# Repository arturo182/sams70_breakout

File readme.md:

# Atmel/Microchip SAM S70 breakout board

A fairly simple board which breaks out all the pins of the chip.

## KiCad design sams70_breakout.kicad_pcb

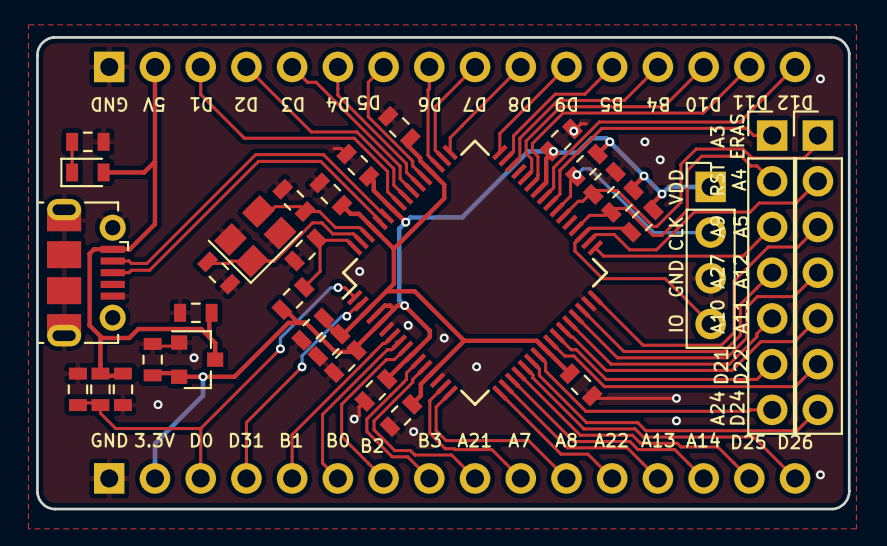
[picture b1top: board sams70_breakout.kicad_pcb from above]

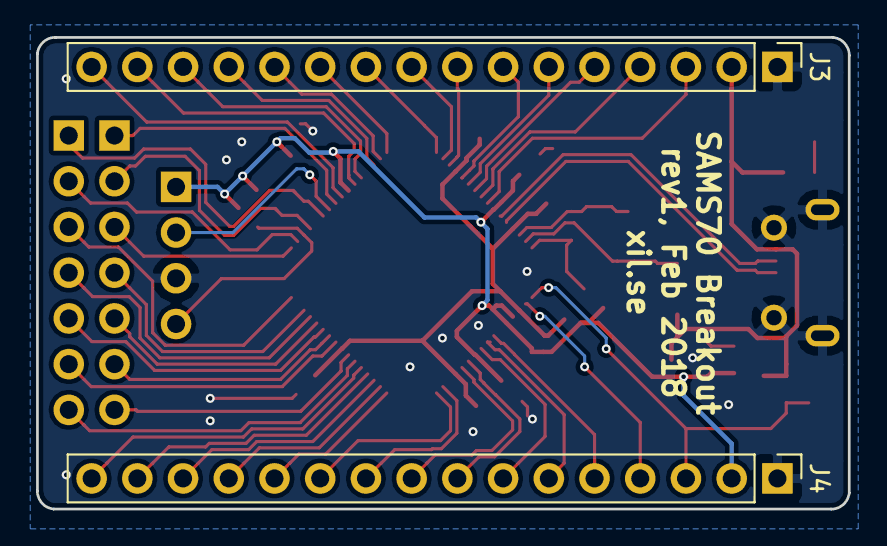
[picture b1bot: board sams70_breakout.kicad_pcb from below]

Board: 2 copper layers, 45.1 x 26.2 mm, 34 parts (2 on the bottom side), 54 nets.

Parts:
C1, C14: 4.7uF; C_0603_1608Metric
C2, C3: 12pF; C_0603_1608Metric
C4, C5, C6, C7, C8, C9, C11, C12, C13: 0.1uF; C_0603_1608Metric
C10, C15, C16: 1uF; C_0603_1608Metric
D1: PWR; LED_0603_1608Metric
J1: USB_OTG; USB_Micro-B_Molex-105017-0001
J2: Conn_01x04; PinHeader_1x04_P2.54mm_Vertical
J3, J4: Conn_01x16; PinHeader_1x16_P2.54mm_Vertical
J5, J6: Conn_01x07; PinHeader_1x07_P2.54mm_Vertical
R1: 15k; R_0603_1608Metric
R2: 22k; R_0603_1608Metric
R3, R5, R6, R7: 10K; R_0603_1608Metric
R4: 2.2R; R_0603_1608Metric
R8: 560R; R_0603_1608Metric
U1: ATSAME70J20A-AN; LQFP-64_10x10mm_P0.5mm
U2: XC6206P332MR; SOT-23
Y1: 16MHz; Crystal_SMD_3225-4Pin_3.2x2.5mm

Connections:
+1V2: C4.1, C5.1, C6.1, C10.2, C11.2, C13.2, U1.3, U1.13, U1.24, U1.52, U1.61
+3V3: C7.1, C8.1, C9.1, C12.2, C16.1, J2.1, J4.2, R3.1, R4.1, R6.1, R7.1, U1.4, U1.5, U1.10, U1.42, U1.58, U2.2
/ERASE: J6.1, R5.1, U1.38
/PA3: J5.1, U1.40
/PA4: J6.2, U1.34
/PA5: J6.3, U1.32
/PA7: J4.10, U1.15
/PA8: J4.11, U1.16
/PA9: J5.3, U1.33
/PA10: J5.5, U1.28
/PA11: J6.5, U1.27
/PA12: J6.4, U1.29
/PA13: J4.13, U1.18
/PA14: J4.14, U1.19
/PA21: J4.9, U1.12
/PA22: J4.12, U1.17
/PA24: J5.7, U1.23
/PA27: J5.4, U1.30
/PB0: J4.6, U1.8
/PB1: J4.5, U1.7
/PB2: J4.7, U1.9
/PB3: J4.8, U1.11
/PB4: J3.13, U1.46
/PB5: J3.12, U1.47
/PD0: J4.3, R1.1, R2.1, U1.1
/PD1: J3.3, U1.57
/PD2: J3.4, U1.56
/PD3: J3.5, U1.55
/PD4: J3.6, U1.54
/PD5: J3.7, U1.53
/PD6: J3.8, U1.51
/PD7: J3.9, U1.50
/PD8: J3.10, U1.49
/PD9: J3.11, U1.48
/PD10: J3.14, U1.44
/PD11: J3.15, U1.43
/PD12: J3.16, U1.41
/PD21: J5.6, U1.26
/PD22: J6.6, U1.25
/PD24: J6.7, U1.22
/PD25: J4.15, U1.20
/PD26: J4.16, U1.21
/PD31: J4.4, U1.2
/RESET: J5.2, R3.2, U1.36
/SWCLK: J2.2, R7.2, U1.39
/SWDIO: J2.4, R6.2, U1.35
/USB_D+: J1.3, U1.60
/USB_D-: J1.2, U1.59
/XIN: C2.1, U1.63, Y1.1
/XOUT: C3.1, U1.62, Y1.3
GND: C1.1, C2.2, C3.2, C4.2, C5.2, C6.2, C7.2, C8.2, C9.2, C10.1, C11.1, C12.1, C13.1, C14.1, C15.1, C16.2, J1.5, J1.6, J2.3, J3.1, J4.1, R2.2, R5.2, R8.2, U1.6, U1.14, U1.31, U2.1, Y1.2, Y1.4
unnamed: C14.2, R4.2, U1.64
unnamed: D1.1, R8.1
VBUS: C1.2, C15.2, D1.2, J1.1, J3.2, R1.2, U2.3

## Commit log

2018-02-08 Initial import
2018-02-09 Add PWR LED and update footprints to KiCAD nightly
2018-02-10 Hide C7 silk
2018-02-20 Add readme and move images to a folder
